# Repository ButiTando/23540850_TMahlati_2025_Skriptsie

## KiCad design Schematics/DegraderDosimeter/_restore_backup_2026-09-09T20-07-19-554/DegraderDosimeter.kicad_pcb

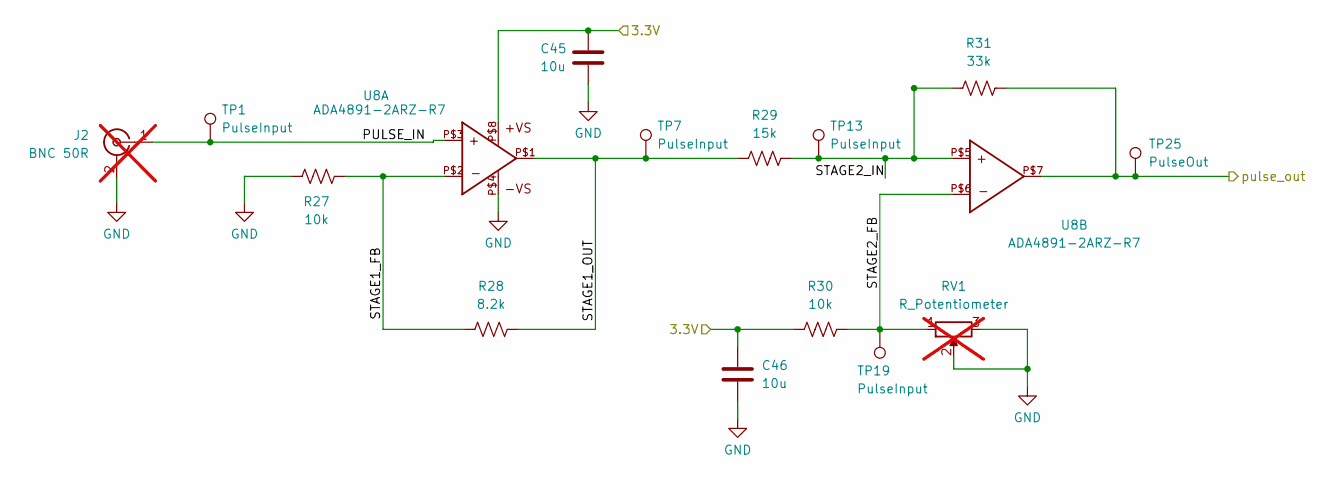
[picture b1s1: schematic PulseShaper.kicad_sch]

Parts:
C45, C46: 10u; C_0603_1608Metric; LCSC C19702
J2: BNC 50R; BNC_Amphenol_B6252HB-NPP3G-50_Horizontal; not fitted
R27, R30: 10k; R_0603_1608Metric; LCSC C25804
R28: 8.2k; R_0603_1608Metric; LCSC C25981
R29: 15k; R_0603_1608Metric; LCSC C22809
R31: 33k; R_0603_1608Metric; LCSC C4216
RV1: R_Potentiometer; Potentiometer_Bourns_3266W_Vertical; not fitted
TP1, TP7, TP13, TP19: PulseInput; TestPoint_Pad_D2.5mm
TP25: PulseOut; TestPoint_Pad_D2.5mm
U8: ADA4891-2ARZ-R7; SOIC8; PARTNO ADA4891-2ARZ-R7CT-ND

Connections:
/MCU_H723/PULSE_1: R31.2, TP25.1 (1_1), U8.P$7; also elsewhere on the board
/PulseShaper1/3.3V: C45.1, C46.1, R30.1, U8.P$8
/PulseShaper1/PULSE_IN: J2.1 (In), TP1.1 (1_1), U8.P$3
/PulseShaper1/STAGE1_FB: R27.2, R28.1, U8.P$2
/PulseShaper1/STAGE1_OUT: R28.2, R29.1, TP7.1 (1_1), U8.P$1
/PulseShaper1/STAGE2_FB: R30.2, RV1.1, TP19.1 (1_1), U8.P$6
/PulseShaper1/STAGE2_IN: R29.2, R31.1, TP13.1 (1_1), U8.P$5
GND: C45.2, C46.2, J2.2 (Ext), R27.1, RV1.2, RV1.3, U8.P$4; also elsewhere on the board

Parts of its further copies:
C47, C48, C49, C50, C51, C52, C53, C54, C55, C56: 10u; C_0603_1608Metric; LCSC C19702
J3, J4, J5, J6, J7: BNC 50R; BNC_Amphenol_B6252HB-NPP3G-50_Horizontal; not fitted
R32, R35, R37, R40, R42, R45, R47, R50, R52, R55: 10k; R_0603_1608Metric; LCSC C25804
R33, R38, R43, R48, R53: 8.2k; R_0603_1608Metric; LCSC C25981
R34, R39, R44, R49, R54: 15k; R_0603_1608Metric; LCSC C22809
R36, R41, R46, R51, R56: 33k; R_0603_1608Metric; LCSC C4216
RV2, RV3, RV4, RV5, RV6: R_Potentiometer; Potentiometer_Bourns_3266W_Vertical; not fitted
TP2, TP3, TP4, TP5, TP6, TP8, TP9, TP10, TP11, TP12, TP14, TP15, TP16, TP17, TP18, TP20, TP21, TP22, TP23, TP24: PulseInput; TestPoint_Pad_D2.5mm
TP26, TP27, TP28, TP29, TP30: PulseOut; TestPoint_Pad_D2.5mm
U9, U10, U11, U12, U13: ADA4891-2ARZ-R7; SOIC8; PARTNO ADA4891-2ARZ-R7CT-ND

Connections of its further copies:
/MCU_H723/PULSE_2: R36.2, TP26.1 (1_1), U9.P$7; also elsewhere on the board
/MCU_H723/PULSE_3: R41.2, TP27.1 (1_1), U10.P$7; also elsewhere on the board
/MCU_H723/PULSE_4: R46.2, TP28.1 (1_1), U11.P$7; also elsewhere on the board
/MCU_H723/PULSE_5: R51.2, TP29.1 (1_1), U12.P$7; also elsewhere on the board
/MCU_H723/PULSE_6: R56.2, TP30.1 (1_1), U13.P$7; also elsewhere on the board
/PulseShaper2/3.3V: C47.1, C48.1, R35.1, U9.P$8
/PulseShaper2/PULSE_IN: J3.1 (In), TP2.1 (1_1), U9.P$3
/PulseShaper2/STAGE1_FB: R32.2, R33.1, U9.P$2
/PulseShaper2/STAGE1_OUT: R33.2, R34.1, TP8.1 (1_1), U9.P$1
/PulseShaper2/STAGE2_FB: R35.2, RV2.1, TP20.1 (1_1), U9.P$6
/PulseShaper2/STAGE2_IN: R34.2, R36.1, TP14.1 (1_1), U9.P$5
/PulseShaper3/3.3V: C49.1, C50.1, R40.1, U10.P$8
/PulseShaper3/PULSE_IN: J4.1 (In), TP3.1 (1_1), U10.P$3
/PulseShaper3/STAGE1_FB: R37.2, R38.1, U10.P$2
/PulseShaper3/STAGE1_OUT: R38.2, R39.1, TP9.1 (1_1), U10.P$1
/PulseShaper3/STAGE2_FB: R40.2, RV3.1, TP21.1 (1_1), U10.P$6
/PulseShaper3/STAGE2_IN: R39.2, R41.1, TP15.1 (1_1), U10.P$5
/PulseShaper4/3.3V: C51.1, C52.1, R45.1, U11.P$8
/PulseShaper4/PULSE_IN: J5.1 (In), TP4.1 (1_1), U11.P$3
/PulseShaper4/STAGE1_FB: R42.2, R43.1, U11.P$2
/PulseShaper4/STAGE1_OUT: R43.2, R44.1, TP10.1 (1_1), U11.P$1
/PulseShaper4/STAGE2_FB: R45.2, RV4.1, TP22.1 (1_1), U11.P$6
/PulseShaper4/STAGE2_IN: R44.2, R46.1, TP16.1 (1_1), U11.P$5
/PulseShaper5/3.3V: C53.1, C54.1, R50.1, U12.P$8
/PulseShaper5/PULSE_IN: J6.1 (In), TP5.1 (1_1), U12.P$3
/PulseShaper5/STAGE1_FB: R47.2, R48.1, U12.P$2
/PulseShaper5/STAGE1_OUT: R48.2, R49.1, TP11.1 (1_1), U12.P$1
/PulseShaper5/STAGE2_FB: R50.2, RV5.1, TP23.1 (1_1), U12.P$6
/PulseShaper5/STAGE2_IN: R49.2, R51.1, TP17.1 (1_1), U12.P$5
/PulseShaper6/3.3V: C55.1, C56.1, R55.1, U13.P$8
/PulseShaper6/PULSE_IN: J7.1 (In), TP6.1 (1_1), U13.P$3
/PulseShaper6/STAGE1_FB: R52.2, R53.1, U13.P$2
/PulseShaper6/STAGE1_OUT: R53.2, R54.1, TP12.1 (1_1), U13.P$1
/PulseShaper6/STAGE2_FB: R55.2, RV6.1, TP24.1 (1_1), U13.P$6
/PulseShaper6/STAGE2_IN: R54.2, R56.1, TP18.1 (1_1), U13.P$5
GND: C47.2, C48.2, C49.2, C50.2, C51.2, C52.2, C53.2, C54.2, C55.2, C56.2, J3.2 (Ext), J4.2 (Ext), J5.2 (Ext), J6.2 (Ext), J7.2 (Ext), R32.1, R37.1, R42.1, R47.1, R52.1, RV2.2, RV2.3, RV3.2, RV3.3, RV4.2, RV4.3, RV5.2, RV5.3, RV6.2, RV6.3, U9.P$4, U10.P$4, U11.P$4, U12.P$4, U13.P$4; also elsewhere on the board

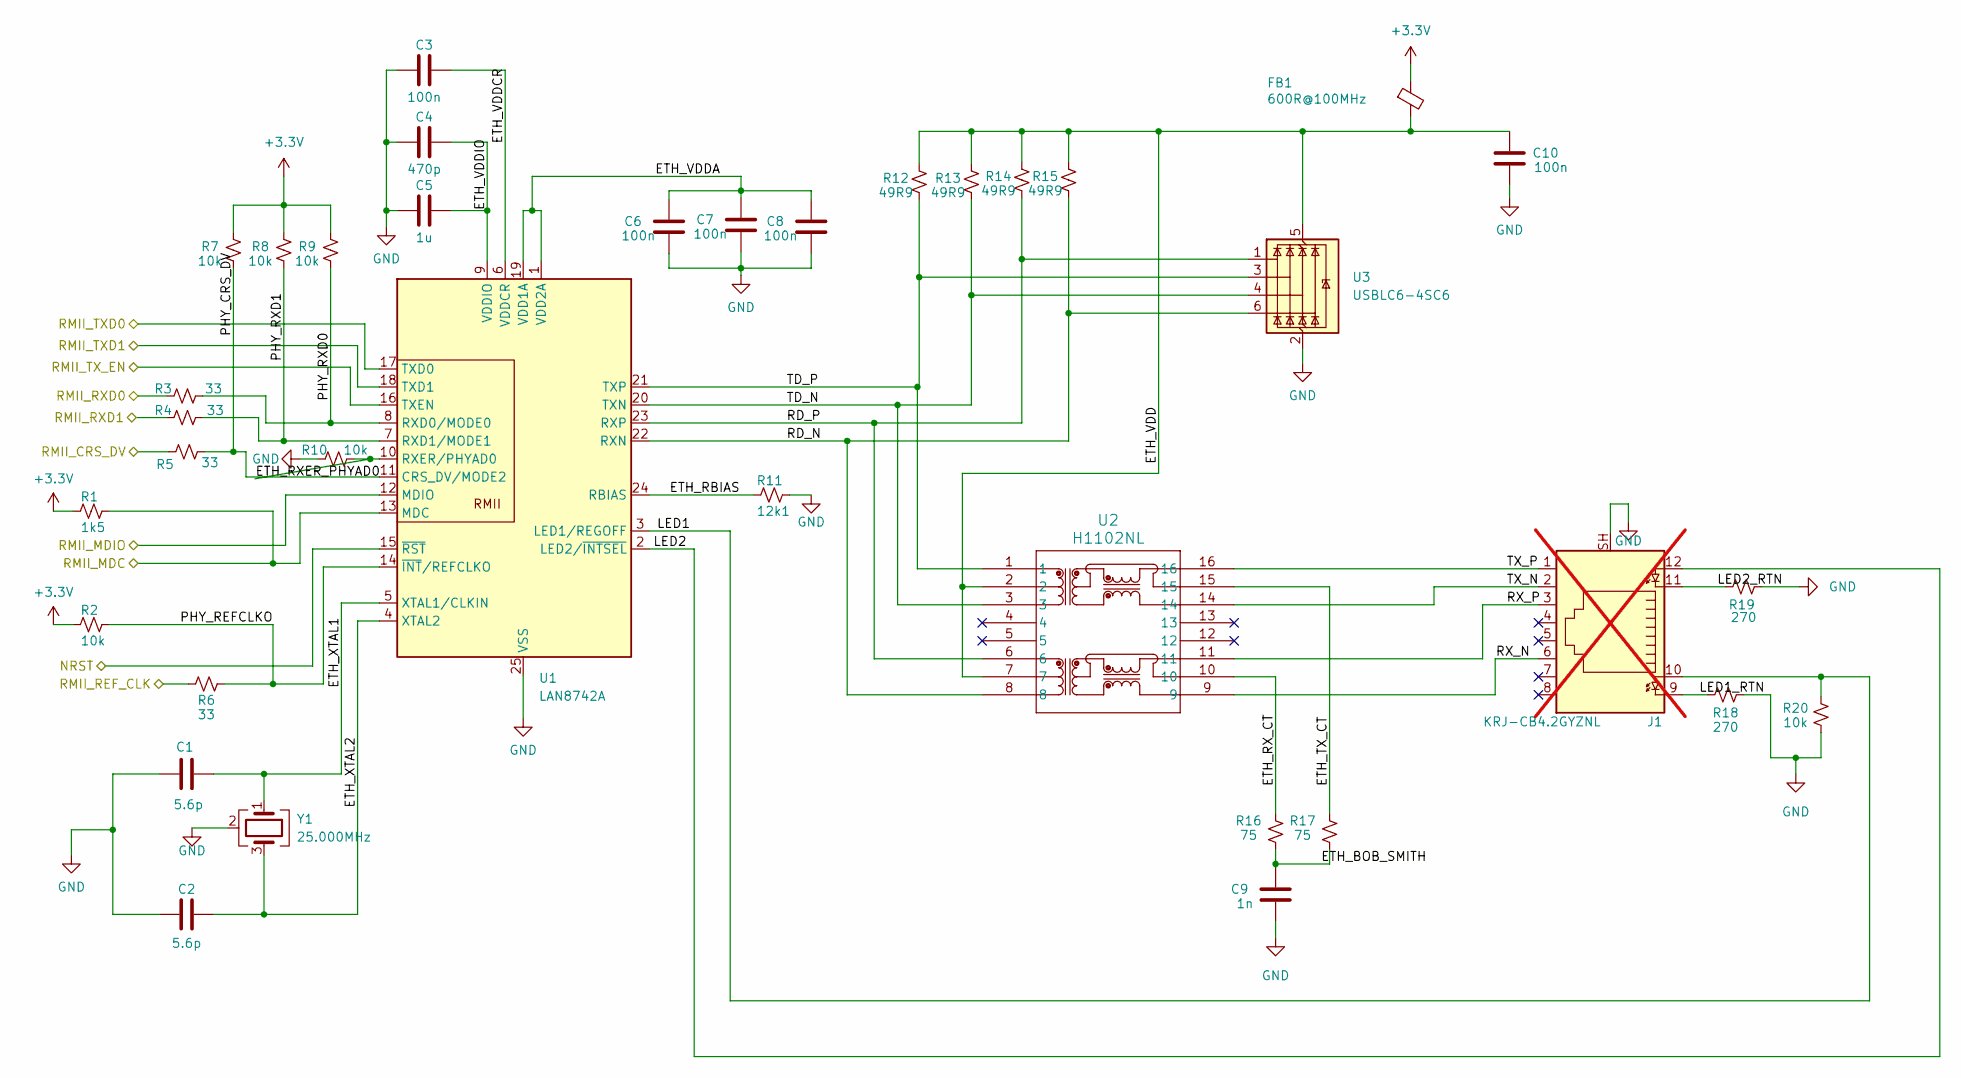
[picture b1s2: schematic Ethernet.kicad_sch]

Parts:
C1, C2: 5.6p; C_0603_1608Metric
C3, C6, C7, C8, C10: 100n; C_0603_1608Metric; LCSC C14663
C4: 470p; C_0603_1608Metric; LCSC C1620
C5: 1u; C_0603_1608Metric; LCSC C15849
C9: 1n; C_1206_3216Metric
FB1: 600R@100MHz; L_0603_1608Metric
J1: KRJ-CB4.2GYZNL; not fitted
R1: 1k5; R_0603_1608Metric; LCSC C22843
R2, R7, R8, R9, R10, R20: 10k; R_0603_1608Metric; LCSC C25804
R3, R4, R5, R6: 33; R_0603_1608Metric; LCSC C23140
R11: 12k1; R_0603_1608Metric
R12, R13, R14, R15: 49R9; R_0603_1608Metric; LCSC C23185
R16, R17: 75; R_0603_1608Metric; LCSC C4275
R18, R19: 270; R_0603_1608Metric; LCSC C22966
U1: LAN8742A; VQFN-24-1EP_4x4mm_P0.5mm_EP2.5x2.5mm_ThermalVias
U2: H1102NL; Transformer_Pulse_H1100NL
U3: USBLC6-4SC6; SOT-23-6
Y1: 25.000MHz; Crystal_SMD_2016-4Pin_2.0x1.6mm

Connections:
+3.3V: FB1.1, R1.1, R2.1, R7.2, R8.2, R9.2; also elsewhere on the board
/Ethernet/ETH_BOB_SMITH: C9.1, R16.2, R17.2
/Ethernet/ETH_RBIAS: R11.1, U1.24 (RBIAS)
/Ethernet/ETH_RXER_PHYAD0: R10.2, U1.10 (RXER/PHYAD0)
/Ethernet/ETH_RX_CT: R16.1, U2.10
/Ethernet/ETH_TX_CT: R17.1, U2.15
/Ethernet/ETH_VDD: C10.1, FB1.2, R12.2, R13.2, R14.2, R15.2, U2.2, U2.7, U3.5 (VBUS)
/Ethernet/ETH_VDDA: C6.1, C7.1, C8.1, U1.1 (VDD2A), U1.19 (VDD1A)
/Ethernet/ETH_VDDCR: C3.1, U1.6 (VDDCR)
/Ethernet/ETH_VDDIO: C4.1, C5.1, U1.9 (VDDIO)
/Ethernet/ETH_XTAL1: C1.2, U1.5 (XTAL1/CLKIN), Y1.1
/Ethernet/ETH_XTAL2: C2.2, U1.4 (XTAL2), Y1.3
/Ethernet/LED1: J1.10, R20.2, U1.3 (LED1/REGOFF)
/Ethernet/LED1_RTN: J1.9, R18.2
/Ethernet/LED2: J1.12, U1.2 (LED2/~INTSEL)
/Ethernet/LED2_RTN: J1.11, R19.1
/Ethernet/NRST: U1.15 (~RST)
/Ethernet/PHY_CRS_DV: R5.2, R7.1, U1.11 (CRS_DV/MODE2)
/Ethernet/PHY_REFCLKO: R2.2, R6.2, U1.14 (~INT/REFCLKO)
/Ethernet/PHY_RXD0: R3.2, R9.1, U1.8 (RXD0/MODE0)
/Ethernet/PHY_RXD1: R4.2, R8.1, U1.7 (RXD1/MODE1)
/Ethernet/RD_N: R15.1, U1.22 (RXN), U2.8, U3.6 (I/O4)
/Ethernet/RD_P: R14.1, U1.23 (RXP), U2.6, U3.1 (I/O1)
/Ethernet/RMII_CRS_DV: R5.1; also elsewhere on the board
/Ethernet/RMII_MDC: R1.2, U1.13 (MDC); also elsewhere on the board
/Ethernet/RMII_MDIO: U1.12 (MDIO); also elsewhere on the board
/Ethernet/RMII_REF_CLK: R6.1; also elsewhere on the board
/Ethernet/RMII_RXD0: R3.1; also elsewhere on the board
/Ethernet/RMII_RXD1: R4.1; also elsewhere on the board
/Ethernet/RMII_TXD0: U1.17 (TXD0); also elsewhere on the board
/Ethernet/RMII_TXD1: U1.18 (TXD1); also elsewhere on the board
/Ethernet/RMII_TX_EN: U1.16 (TXEN); also elsewhere on the board
/Ethernet/RX_N: J1.6, U2.9
/Ethernet/RX_P: J1.3, U2.11
/Ethernet/TD_N: R13.1, U1.20 (TXN), U2.3, U3.4 (I/O3)
/Ethernet/TD_P: R12.1, U1.21 (TXP), U2.1, U3.3 (I/O2)
/Ethernet/TX_N: J1.2, U2.14
/Ethernet/TX_P: J1.1, U2.16
GND: C1.1, C2.1, C3.2, C4.2, C5.2, C6.2, C7.2, C8.2, C9.2, C10.2, J1.SH, R10.1, R11.2, R18.1, R19.2, R20.1, U1.25 (VSS), U3.2 (GND), Y1.2 (G), Y1.4 (G); also elsewhere on the board

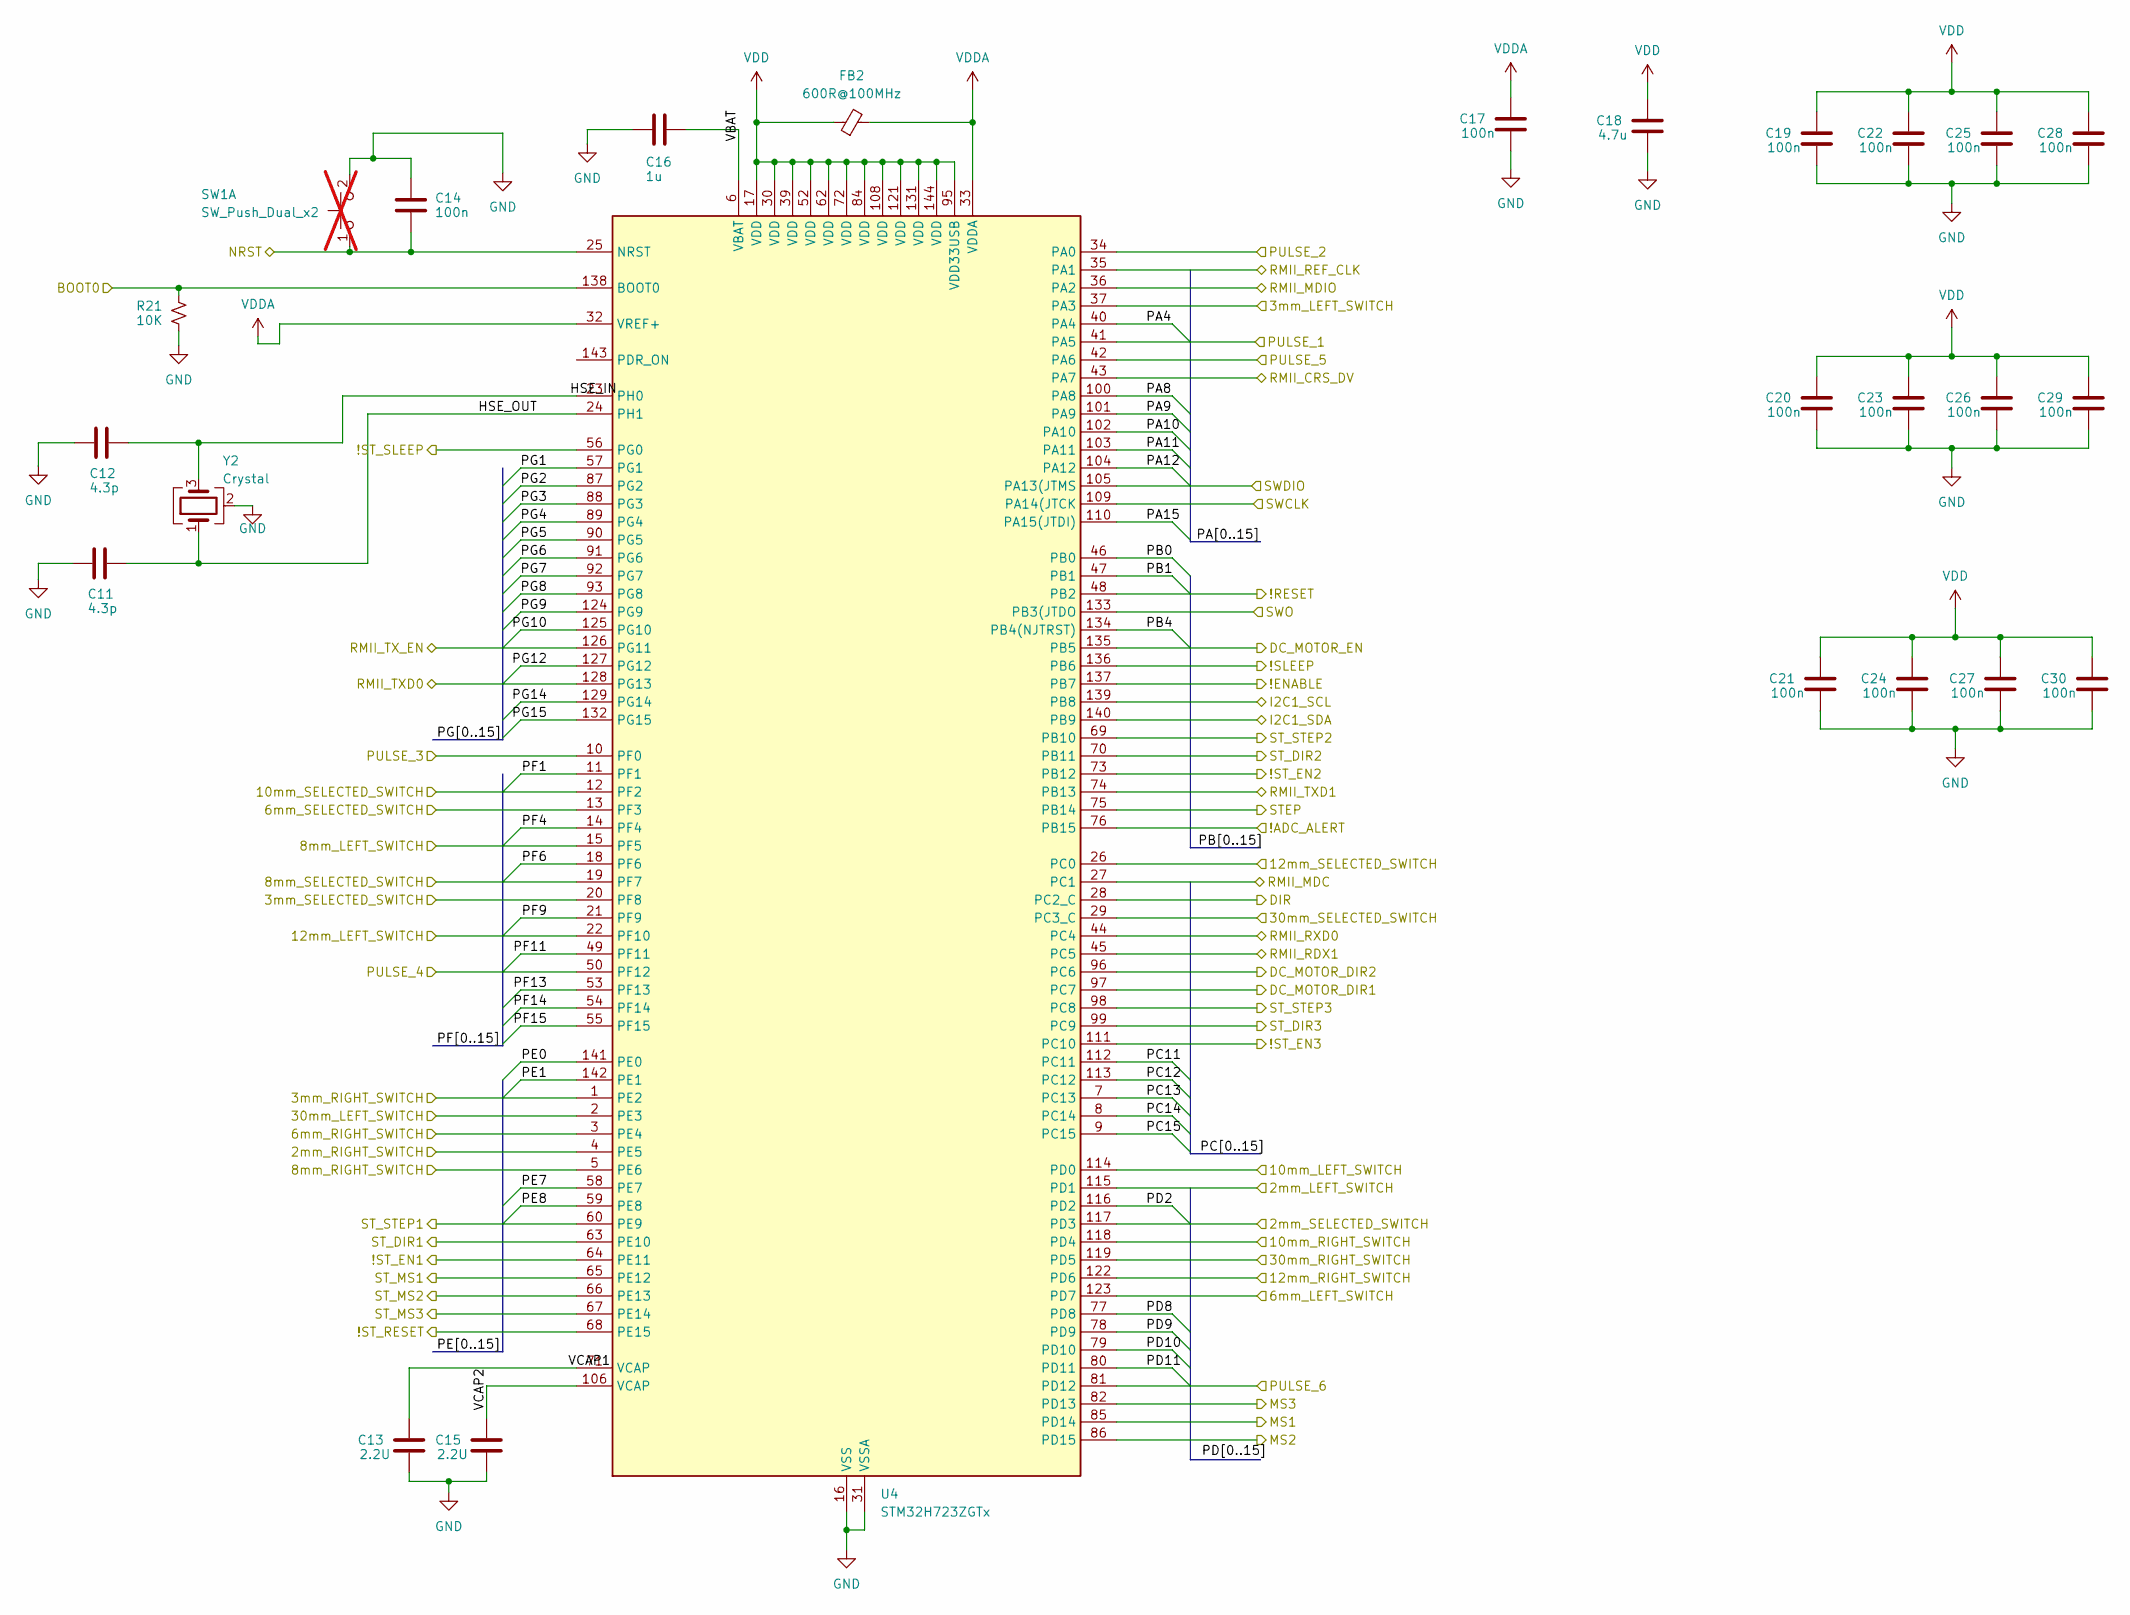
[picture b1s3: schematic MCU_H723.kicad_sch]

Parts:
C11, C12: 4.3p; C_0603_1608Metric
C13, C15: 2.2U; C_0603_1608Metric
C14, C17, C19, C20, C21, C22, C23, C24, C25, C26, C27, C28, C29, C30: 100n; C_0603_1608Metric; LCSC C14663
C16: 1u; C_0603_1608Metric; LCSC C15849
C18: 4.7u; C_0603_1608Metric; LCSC C19666
FB2: 600R@100MHz; L_0603_1608Metric
R21: 10K; R_0603_1608Metric; LCSC C25804
SW1: SW_Push_Dual_x2; SW_Tactile_Straight_KSL0Axx1LFTR; not fitted
U4: STM32H723ZGTx; LQFP-144_20x20mm_P0.5mm
Y2: Crystal; Crystal_SMD_Abracon_ABM10-4Pin_2.5x2.0mm

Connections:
/ADC_I2C/!ADC_ALERT: U4.76 (PB15); also elsewhere on the board
/ADC_I2C/I2C1_SCL: U4.139 (PB8); also elsewhere on the board
/ADC_I2C/I2C1_SDA: U4.140 (PB9); also elsewhere on the board
/Debugger/SWCLK: U4.109 (PA14(JTCK); also elsewhere on the board
/Debugger/SWDIO: U4.105 (PA13(JTMS); also elsewhere on the board
/Debugger/SWO: U4.133 (PB3(JTDO); also elsewhere on the board
/Degrader/2mm_LEFT_SWITCH: U4.115 (PD1); also elsewhere on the board
/Degrader/2mm_RIGHT_SWITCH: U4.4 (PE5); also elsewhere on the board
/Degrader/2mm_SELECTED_SWITCH: U4.117 (PD3); also elsewhere on the board
/Degrader/3mm_LEFT_SWITCH: U4.37 (PA3); also elsewhere on the board
/Degrader/3mm_RIGHT_SWITCH: U4.1 (PE2); also elsewhere on the board
/Degrader/3mm_SELECTED_SWITCH: U4.20 (PF8); also elsewhere on the board
/Degrader/6mm_LEFT_SWITCH: U4.123 (PD7); also elsewhere on the board
/Degrader/6mm_RIGHT_SWITCH: U4.3 (PE4); also elsewhere on the board
/Degrader/6mm_SELECTED_SWITCH: U4.13 (PF3); also elsewhere on the board
/Degrader/8mm_LEFT_SWITCH: U4.15 (PF5); also elsewhere on the board
/Degrader/8mm_RIGHT_SWITCH: U4.5 (PE6); also elsewhere on the board
/Degrader/8mm_SELECTED_SWITCH: U4.19 (PF7); also elsewhere on the board
/Degrader/10mm_LEFT_SWITCH: U4.114 (PD0); also elsewhere on the board
/Degrader/10mm_RIGHT_SWITCH: U4.118 (PD4); also elsewhere on the board
/Degrader/10mm_SELECTED_SWITCH: U4.12 (PF2); also elsewhere on the board
/Degrader/12mm_LEFT_SWITCH: U4.22 (PF10); also elsewhere on the board
/Degrader/12mm_RIGHT_SWITCH: U4.122 (PD6); also elsewhere on the board
/Degrader/12mm_SELECTED_SWITCH: U4.26 (PC0); also elsewhere on the board
/Degrader/30mm_LEFT_SWITCH: U4.2 (PE3); also elsewhere on the board
/Degrader/30mm_RIGHT_SWITCH: U4.119 (PD5); also elsewhere on the board
/Degrader/30mm_SELECTED_SWITCH: U4.29 (PC3_C); also elsewhere on the board
/Degrader/!ENABLE: U4.137 (PB7); also elsewhere on the board
/Degrader/!RESET: U4.48 (PB2); also elsewhere on the board
/Degrader/!SLEEP: U4.136 (PB6); also elsewhere on the board
/Degrader/DC_MOTOR_DIR1: U4.97 (PC7); also elsewhere on the board
/Degrader/DC_MOTOR_DIR2: U4.96 (PC6); also elsewhere on the board
/Degrader/DC_MOTOR_EN: U4.135 (PB5); also elsewhere on the board
/Degrader/DIR: U4.28 (PC2_C); also elsewhere on the board
/Degrader/MS1: U4.85 (PD14); also elsewhere on the board
/Degrader/MS2: U4.86 (PD15); also elsewhere on the board
/Degrader/MS3: U4.82 (PD13); also elsewhere on the board
/Degrader/STEP: U4.75 (PB14); also elsewhere on the board
/Ethernet/RMII_CRS_DV: U4.43 (PA7); also elsewhere on the board
/Ethernet/RMII_MDC: U4.27 (PC1); also elsewhere on the board
/Ethernet/RMII_MDIO: U4.36 (PA2); also elsewhere on the board
/Ethernet/RMII_REF_CLK: U4.35 (PA1); also elsewhere on the board
/Ethernet/RMII_RXD0: U4.44 (PC4); also elsewhere on the board
/Ethernet/RMII_RXD1: U4.45 (PC5); also elsewhere on the board
/Ethernet/RMII_TXD0: U4.128 (PG13); also elsewhere on the board
/Ethernet/RMII_TXD1: U4.74 (PB13); also elsewhere on the board
/Ethernet/RMII_TX_EN: U4.126 (PG11); also elsewhere on the board
/MCU_H723/!ST_EN1: U4.64 (PE11); also elsewhere on the board
/MCU_H723/!ST_EN2: U4.73 (PB12); also elsewhere on the board
/MCU_H723/!ST_EN3: U4.111 (PC10); also elsewhere on the board
/MCU_H723/!ST_RESET: U4.68 (PE15); also elsewhere on the board
/MCU_H723/!ST_SLEEP: U4.56 (PG0); also elsewhere on the board
/MCU_H723/BOOT0: R21.1, U4.138 (BOOT0)
/MCU_H723/HSE_IN: C12.2, U4.23 (PH0), Y2.3
/MCU_H723/HSE_OUT: C11.2, U4.24 (PH1), Y2.1
/MCU_H723/NRST: C14.2, SW1.1 (C), U4.25 (NRST)
/MCU_H723/PA4: U4.40 (PA4)
/MCU_H723/PA8: U4.100 (PA8)
/MCU_H723/PA9: U4.101 (PA9)
/MCU_H723/PA10: U4.102 (PA10)
/MCU_H723/PA11: U4.103 (PA11)
/MCU_H723/PA12: U4.104 (PA12)
/MCU_H723/PA15: U4.110 (PA15(JTDI))
/MCU_H723/PB0: U4.46 (PB0)
/MCU_H723/PB1: U4.47 (PB1)
/MCU_H723/PB4: U4.134 (PB4(NJTRST))
/MCU_H723/PC11: U4.112 (PC11)
/MCU_H723/PC12: U4.113 (PC12)
/MCU_H723/PC13: U4.7 (PC13)
/MCU_H723/PC14: U4.8 (PC14)
/MCU_H723/PC15: U4.9 (PC15)
/MCU_H723/PD2: U4.116 (PD2)
/MCU_H723/PD8: U4.77 (PD8)
/MCU_H723/PD9: U4.78 (PD9)
/MCU_H723/PD10: U4.79 (PD10)
/MCU_H723/PD11: U4.80 (PD11)
/MCU_H723/PE0: U4.141 (PE0)
/MCU_H723/PE1: U4.142 (PE1)
/MCU_H723/PE7: U4.58 (PE7)
/MCU_H723/PE8: U4.59 (PE8)
/MCU_H723/PF1: U4.11 (PF1)
/MCU_H723/PF4: U4.14 (PF4)
/MCU_H723/PF6: U4.18 (PF6)
/MCU_H723/PF9: U4.21 (PF9)
/MCU_H723/PF11: U4.49 (PF11)
/MCU_H723/PF13: U4.53 (PF13)
/MCU_H723/PF14: U4.54 (PF14)
/MCU_H723/PF15: U4.55 (PF15)
/MCU_H723/PG1: U4.57 (PG1)
/MCU_H723/PG2: U4.87 (PG2)
/MCU_H723/PG3: U4.88 (PG3)
/MCU_H723/PG4: U4.89 (PG4)
/MCU_H723/PG5: U4.90 (PG5)
/MCU_H723/PG6: U4.91 (PG6)
/MCU_H723/PG7: U4.92 (PG7)
/MCU_H723/PG8: U4.93 (PG8)
/MCU_H723/PG9: U4.124 (PG9)
/MCU_H723/PG10: U4.125 (PG10)
/MCU_H723/PG12: U4.127 (PG12)
/MCU_H723/PG14: U4.129 (PG14)
/MCU_H723/PG15: U4.132 (PG15)
/MCU_H723/PULSE_1: U4.41 (PA5); also elsewhere on the board
/MCU_H723/PULSE_2: U4.34 (PA0); also elsewhere on the board
/MCU_H723/PULSE_3: U4.10 (PF0); also elsewhere on the board
/MCU_H723/PULSE_4: U4.50 (PF12); also elsewhere on the board
/MCU_H723/PULSE_5: U4.42 (PA6); also elsewhere on the board
/MCU_H723/PULSE_6: U4.81 (PD12); also elsewhere on the board
/MCU_H723/ST_DIR1: U4.63 (PE10); also elsewhere on the board
/MCU_H723/ST_DIR2: U4.70 (PB11); also elsewhere on the board
/MCU_H723/ST_DIR3: U4.99 (PC9); also elsewhere on the board
/MCU_H723/ST_MS1: U4.65 (PE12); also elsewhere on the board
/MCU_H723/ST_MS2: U4.66 (PE13); also elsewhere on the board
/MCU_H723/ST_MS3: U4.67 (PE14); also elsewhere on the board
/MCU_H723/ST_STEP1: U4.60 (PE9); also elsewhere on the board
/MCU_H723/ST_STEP2: U4.69 (PB10); also elsewhere on the board
/MCU_H723/ST_STEP3: U4.98 (PC8); also elsewhere on the board
/MCU_H723/VBAT: C16.1, U4.6 (VBAT)
/MCU_H723/VCAP1: C13.1, U4.71 (VCAP)
/MCU_H723/VCAP2: C15.1, U4.106 (VCAP)
GND: C11.1, C12.1, C13.2, C14.1, C15.2, C16.2, C17.2, C18.2, C19.2, C20.2, C21.2, C22.2, C23.2, C24.2, C25.2, C26.2, C27.2, C28.2, C29.2, C30.2, R21.2, SW1.2 (D), U4.16 (VSS), U4.31 (VSSA), U4.38 (VSS), U4.51 (VSS), U4.61 (VSS), U4.83 (VSS), U4.94 (VSS), U4.107 (VSS), U4.120 (VSS), U4.130 (VSS), Y2.2 (G), Y2.4 (G); also elsewhere on the board
VDD: C18.1, C19.1, C20.1, C21.1, C22.1, C23.1, C24.1, C25.1, C26.1, C27.1, C28.1, C29.1, C30.1, FB2.1, U4.17 (VDD), U4.30 (VDD), U4.39 (VDD), U4.52 (VDD), U4.62 (VDD), U4.72 (VDD), U4.84 (VDD), U4.95 (VDD33USB), U4.108 (VDD), U4.121 (VDD), U4.131 (VDD), U4.144 (VDD)
VDDA: C17.1, FB2.2, U4.32 (VREF+), U4.33 (VDDA)

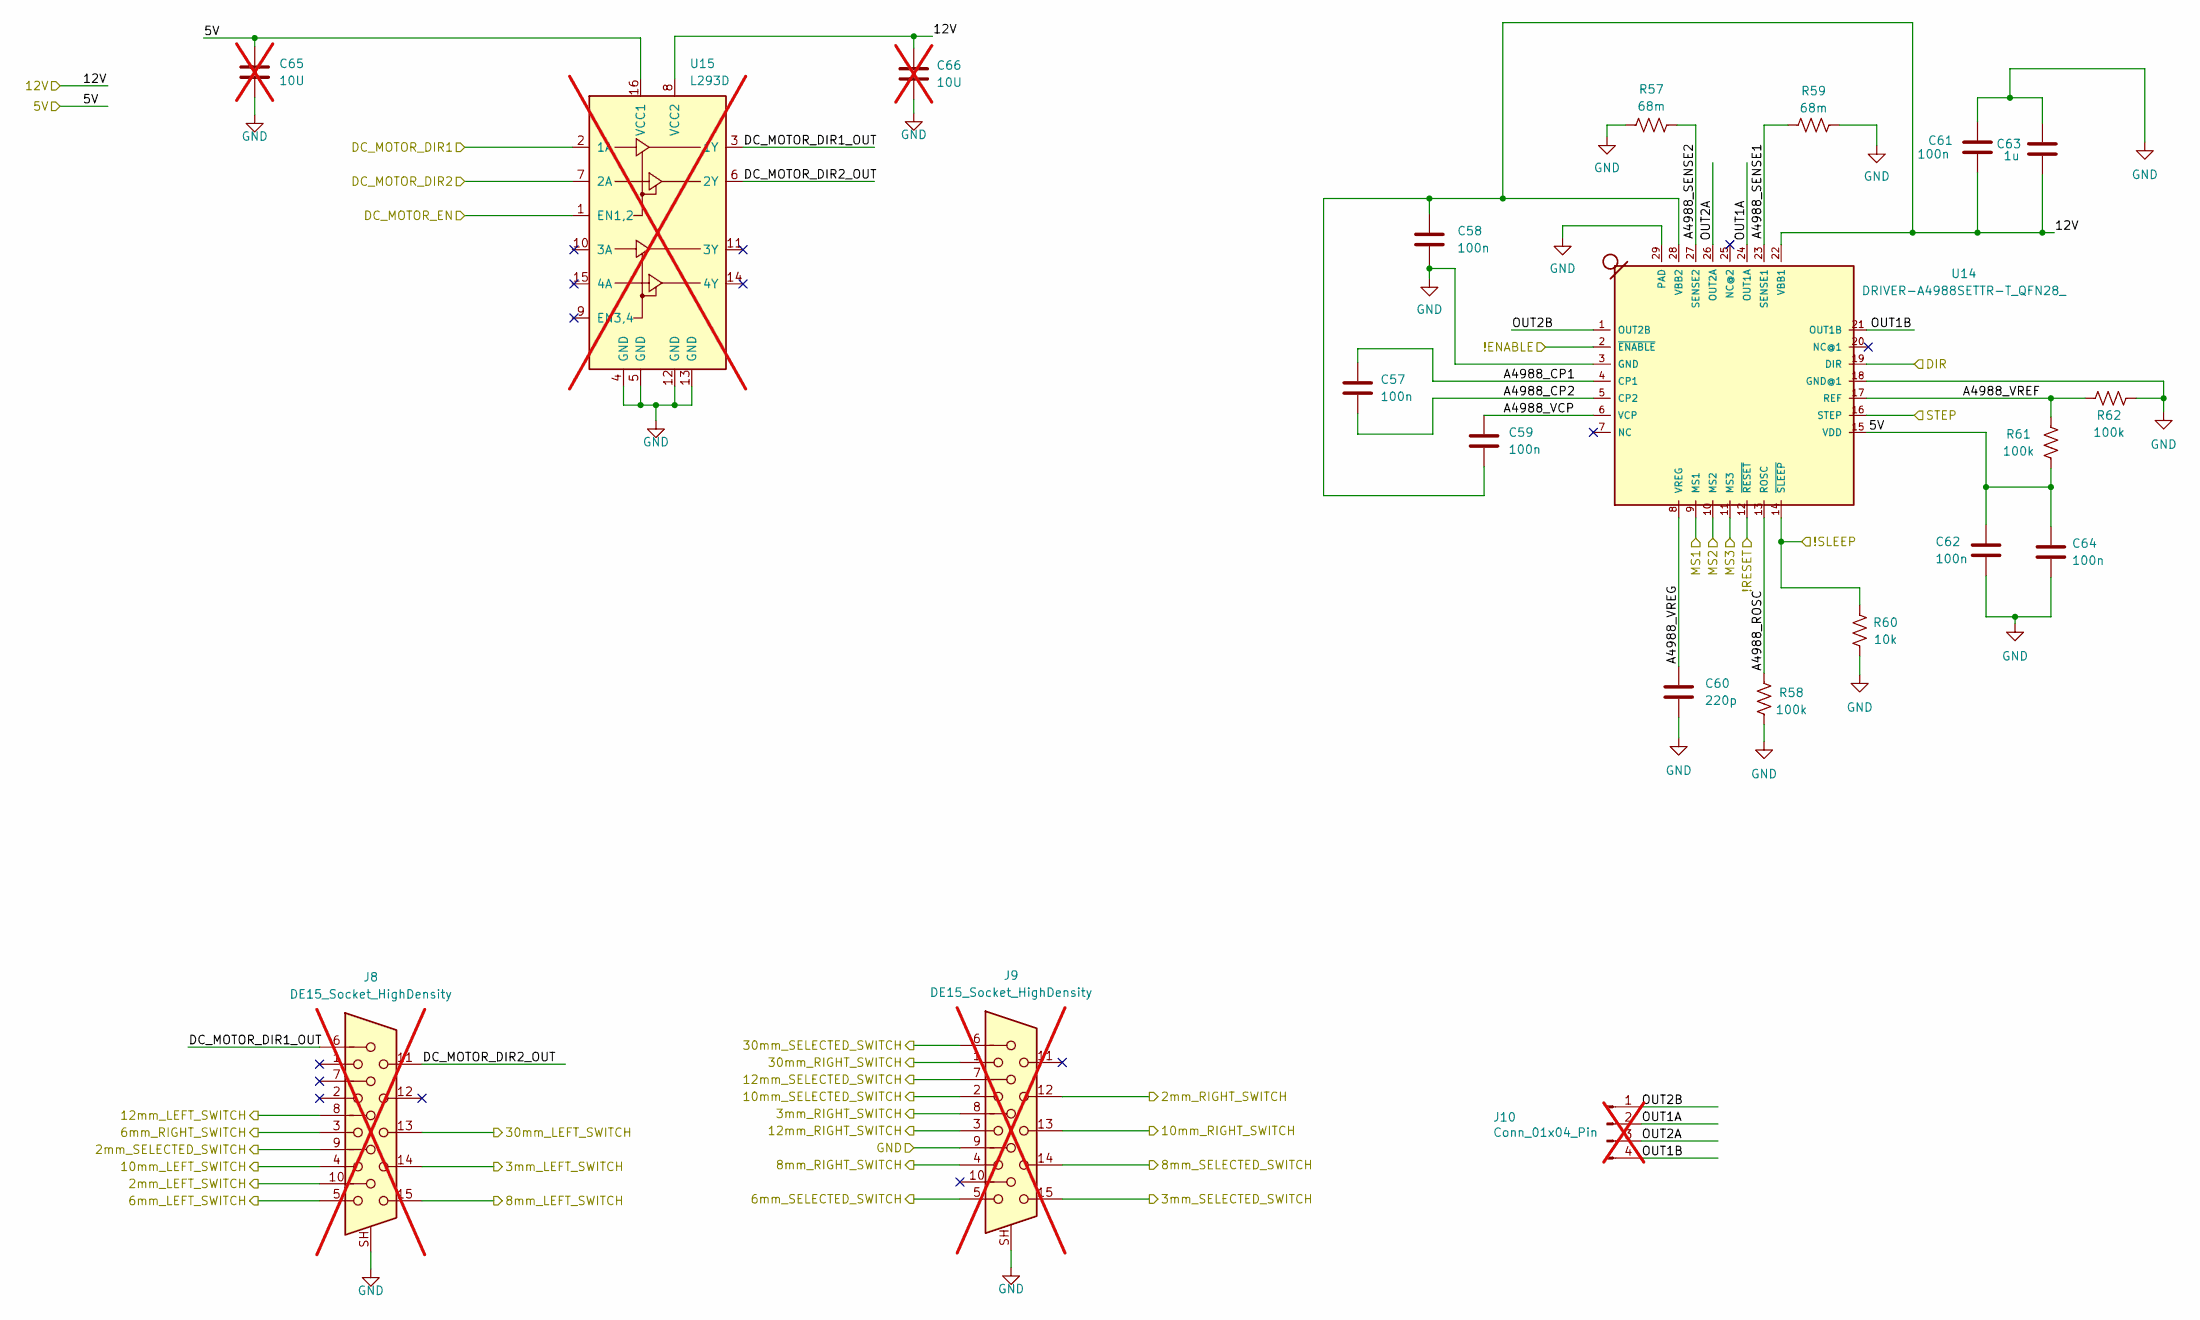
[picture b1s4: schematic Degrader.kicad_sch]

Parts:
C57, C58, C59, C61, C62, C64: 100n; C_0603_1608Metric; LCSC C14663
C60: 220p; C_0603_1608Metric; LCSC C1603
C63: 1u; C_0603_1608Metric; LCSC C15849
C65, C66: 10U; CP_Radial_D10.0mm_P5.00mm; not fitted
J8, J9: DE15_Socket_HighDensity; CONN_HDE15P_AMP; not fitted
J10: Conn_01x04_Pin; SolderWire-2sqmm_1x04_P7.8mm_D2mm_OD3.9mm; not fitted
R57, R59: 68m; R_1206_3216Metric_Pad1.30x1.75mm_HandSolder
R58, R61, R62: 100k; R_0603_1608Metric; LCSC C25803
R60: 10k; R_0603_1608Metric; LCSC C25804
U14: DRIVER-A4988SETTR-T_QFN28_; QFN28G_0.5-5X5MM; MPN A4988SETTR-T
U15: L293D; DIP-16_W7.62mm; not fitted

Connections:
/Degrader/2mm_LEFT_SWITCH: J8.10; also elsewhere on the board
/Degrader/2mm_RIGHT_SWITCH: J9.12; also elsewhere on the board
/Degrader/2mm_SELECTED_SWITCH: J8.9; also elsewhere on the board
/Degrader/3mm_LEFT_SWITCH: J8.14; also elsewhere on the board
/Degrader/3mm_RIGHT_SWITCH: J9.8; also elsewhere on the board
/Degrader/3mm_SELECTED_SWITCH: J9.15; also elsewhere on the board
/Degrader/5V: C62.1, C64.1, C65.1, R61.2, U14.15 (VDD), U15.16 (VCC1)
/Degrader/6mm_LEFT_SWITCH: J8.5; also elsewhere on the board
/Degrader/6mm_RIGHT_SWITCH: J8.3; also elsewhere on the board
/Degrader/6mm_SELECTED_SWITCH: J9.5; also elsewhere on the board
/Degrader/8mm_LEFT_SWITCH: J8.15; also elsewhere on the board
/Degrader/8mm_RIGHT_SWITCH: J9.4; also elsewhere on the board
/Degrader/8mm_SELECTED_SWITCH: J9.14; also elsewhere on the board
/Degrader/10mm_LEFT_SWITCH: J8.4; also elsewhere on the board
/Degrader/10mm_RIGHT_SWITCH: J9.13; also elsewhere on the board
/Degrader/10mm_SELECTED_SWITCH: J9.2; also elsewhere on the board
/Degrader/12V: C58.1, C59.2, C61.1, C63.1, C66.1, U14.22 (VBB1), U14.28 (VBB2), U15.8 (VCC2)
/Degrader/12mm_LEFT_SWITCH: J8.8; also elsewhere on the board
/Degrader/12mm_RIGHT_SWITCH: J9.3; also elsewhere on the board
/Degrader/12mm_SELECTED_SWITCH: J9.7; also elsewhere on the board
/Degrader/30mm_LEFT_SWITCH: J8.13; also elsewhere on the board
/Degrader/30mm_RIGHT_SWITCH: J9.1; also elsewhere on the board
/Degrader/30mm_SELECTED_SWITCH: J9.6; also elsewhere on the board
/Degrader/!ENABLE: U14.2 (~ENABLE); also elsewhere on the board
/Degrader/!RESET: U14.12 (~RESET); also elsewhere on the board
/Degrader/!SLEEP: R60.1, U14.14 (~SLEEP); also elsewhere on the board
/Degrader/A4988_CP1: C57.1, U14.4 (CP1)
/Degrader/A4988_CP2: C57.2, U14.5 (CP2)
/Degrader/A4988_ROSC: R58.1, U14.13 (ROSC)
/Degrader/A4988_SENSE1: R59.2, U14.23 (SENSE1)
/Degrader/A4988_SENSE2: R57.1, U14.27 (SENSE2)
/Degrader/A4988_VCP: C59.1, U14.6 (VCP)
/Degrader/A4988_VREF: R61.1, R62.2, U14.17 (REF)
/Degrader/A4988_VREG: C60.1, U14.8 (VREG)
/Degrader/DC_MOTOR_DIR1: U15.2 (1A); also elsewhere on the board
/Degrader/DC_MOTOR_DIR1_OUT: J8.6, U15.3 (1Y)
/Degrader/DC_MOTOR_DIR2: U15.7 (2A); also elsewhere on the board
/Degrader/DC_MOTOR_DIR2_OUT: J8.11, U15.6 (2Y)
/Degrader/DC_MOTOR_EN: U15.1 (EN1,2); also elsewhere on the board
/Degrader/DIR: U14.19 (DIR); also elsewhere on the board
/Degrader/MS1: U14.9 (MS1); also elsewhere on the board
/Degrader/MS2: U14.10 (MS2); also elsewhere on the board
/Degrader/MS3: U14.11 (MS3); also elsewhere on the board
/Degrader/OUT1A: J10.2, U14.24 (OUT1A)
/Degrader/OUT1B: J10.4, U14.21 (OUT1B)
/Degrader/OUT2A: J10.3, U14.26 (OUT2A)
/Degrader/OUT2B: J10.1, U14.1 (OUT2B)
/Degrader/STEP: U14.16 (STEP); also elsewhere on the board
GND: C58.2, C60.2, C61.2, C62.2, C63.2, C64.2, C65.2, C66.2, J8.SH, J9.9, J9.SH, R57.2, R58.2, R59.1, R60.2, R62.1, U14.3 (GND), U14.18 (GND@1), U14.29 (PAD), U15.4 (GND), U15.5 (GND), U15.12 (GND), U15.13 (GND); also elsewhere on the board
